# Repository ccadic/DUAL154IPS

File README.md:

# DUAL154IPS
BreadBoard for Dual 1.54" COLOR TFT DISPLAY

Display: https://www.aliexpress.com/item/New-IPS-1-3-inch-3-3V-12PIN-SPI-HD-Full-Color-TFT-Display-Screen-ST7789/32859374478.html
Joystick https://www.aliexpress.com/item/5pcs-free-shipping-7mm-x-7mm-6-Pin-5-Way-Momentary-Pushbutton-PCB-SMD-SMT-Tactile/32902822257.html

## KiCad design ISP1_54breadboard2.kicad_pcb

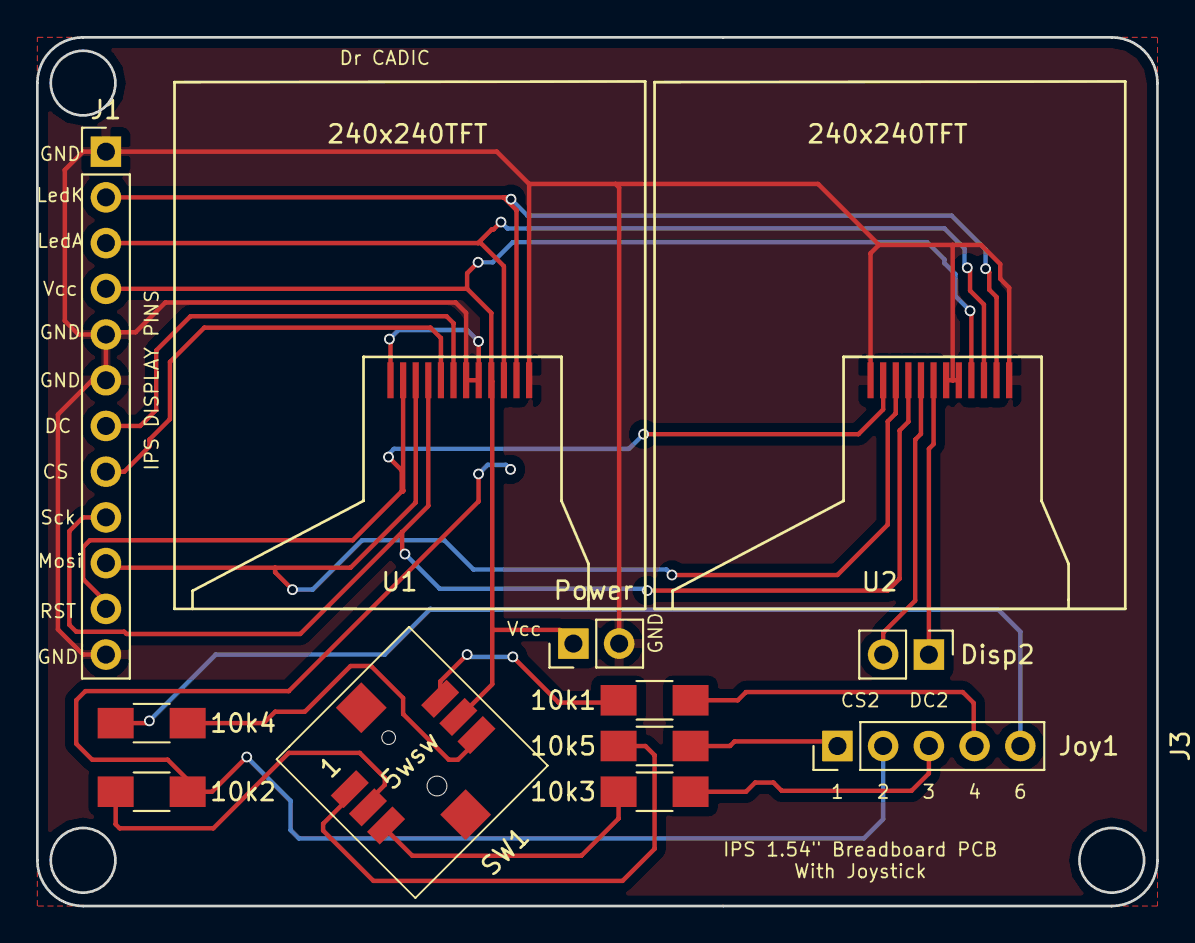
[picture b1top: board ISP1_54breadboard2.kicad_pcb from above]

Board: 2 copper layers, 62.2 x 48.3 mm, 12 parts (0 on the bottom side), 21 nets.

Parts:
10k1, 10k2, 10k3, 10k4, 10k5: R; R_1206_HandSoldering
J1: ConVid; Socket_Strip_Straight_1x12_Pitch2.54mm
J2: Power; Socket_Strip_Straight_1x02_Pitch2.54mm
J3: Disp2; Socket_Strip_Straight_1x02_Pitch2.54mm
Joy1: Conn_01x05; Socket_Strip_Straight_1x05_Pitch2.54mm
SW1: 5W_SW; 5WAY_sw
U1, U2: 240x240TFT; 240240TFT

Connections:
/CS2: J3.2, U2.8
/DC2: J3.1, U2.7
/LEDA: J1.3, U1.3, U2.3
/LEDK: J1.2, U1.2, U2.2
/Mosi: J1.10, U1.10, U2.10
/Reset: J1.11, U1.11, U2.11
/SCK: J1.9, U1.9, U2.9
/VCC: J1.4, J2.1, SW1.5, U1.4, U2.4
GND: J1.1, J1.5, J1.6, J1.12, J2.2, U1.1, U1.5, U1.6, U1.12, U2.1, U2.5, U2.6, U2.12
unnamed: 10k1.1, SW1.1
unnamed: 10k1.2, Joy1.1
unnamed: 10k2.1, SW1.2
unnamed: 10k2.2, Joy1.2
unnamed: 10k3.1, SW1.3
unnamed: 10k3.2, Joy1.3
unnamed: 10k4.1, Joy1.5
unnamed: 10k4.2, SW1.6
unnamed: 10k5.1, Joy1.4
unnamed: 10k5.2, SW1.4
unnamed: J1.7, U1.7
unnamed: J1.8, U1.8
